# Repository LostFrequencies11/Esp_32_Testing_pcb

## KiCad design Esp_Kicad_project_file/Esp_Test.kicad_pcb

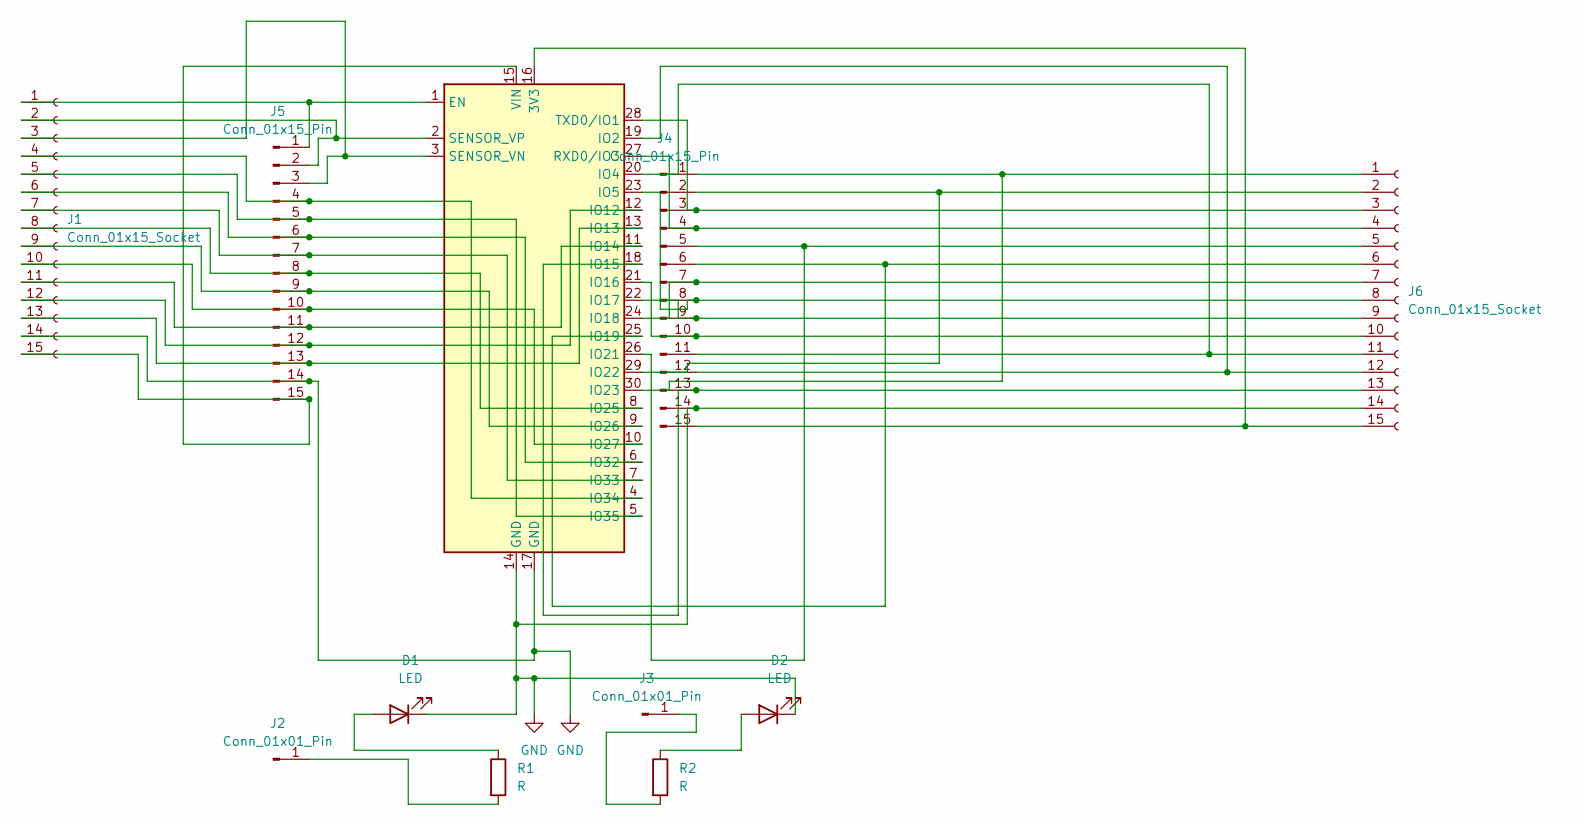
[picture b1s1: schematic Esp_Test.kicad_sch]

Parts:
D1, D2: LED; LED_D5.0mm_Clear
J1, J6: Conn_01x15_Socket; PinHeader_1x15_P2.54mm_Vertical
J2, J3: Conn_01x01_Pin; PinHeader_1x01_P2.54mm_Vertical
J4, J5: Conn_01x15_Pin; Molex_KK-254_AE-6410-15A_1x15_P2.54mm_Vertical
R1, R2: R; R_Axial_DIN0204_L3.6mm_D1.6mm_P7.62mm_Horizontal
U1: ESP32_DevKit_V1_DOIT; esp32_devkit_v1_doit

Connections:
GND: D1.1 (K), D2.1 (K), J1.14, J4.14, J5.14, J6.14, U1.14 (GND), U1.17 (GND)
unnamed: D1.2 (A), R1.1
unnamed: D2.2 (A), R2.1
unnamed: J1.1, J5.1, U1.1 (EN)
unnamed: J1.2, J5.2, U1.2 (SENSOR_VP)
unnamed: J1.3, J5.3, U1.3 (SENSOR_VN)
unnamed: J1.4, J5.4, U1.4 (IO34)
unnamed: J1.5, J5.5, U1.5 (IO35)
unnamed: J1.6, J5.6, U1.6 (IO32)
unnamed: J1.7, J5.7, U1.7 (IO33)
unnamed: J1.8, J5.8, U1.8 (IO25)
unnamed: J1.9, J5.9, U1.9 (IO26)
unnamed: J1.10, J5.10, U1.10 (IO27)
unnamed: J1.11, J5.11, U1.11 (IO14)
unnamed: J1.12, J5.12, U1.12 (IO12)
unnamed: J1.13, J5.13, U1.13 (IO13)
unnamed: J1.15, J5.15, U1.15 (VIN)
unnamed: J2.1, R1.2
unnamed: J3.1, R2.2
unnamed: J4.1, J6.1, U1.30 (IO23)
unnamed: J4.2, J6.2, U1.29 (IO22)
unnamed: J4.3, J6.3, U1.28 (TXD0/IO1)
unnamed: J4.4, J6.4, U1.27 (RXD0/IO3)
unnamed: J4.5, J6.5, U1.26 (IO21)
unnamed: J4.6, J6.6, U1.25 (IO19)
unnamed: J4.7, J6.7, U1.24 (IO18)
unnamed: J4.8, J6.8, U1.23 (IO5)
unnamed: J4.9, J6.9, U1.22 (IO17)
unnamed: J4.10, J6.10, U1.21 (IO16)
unnamed: J4.11, J6.11, U1.20 (IO4)
unnamed: J4.12, J6.12, U1.19 (IO2)
unnamed: J4.13, J6.13, U1.18 (IO15)
unnamed: J4.15, J6.15, U1.16 (3V3)

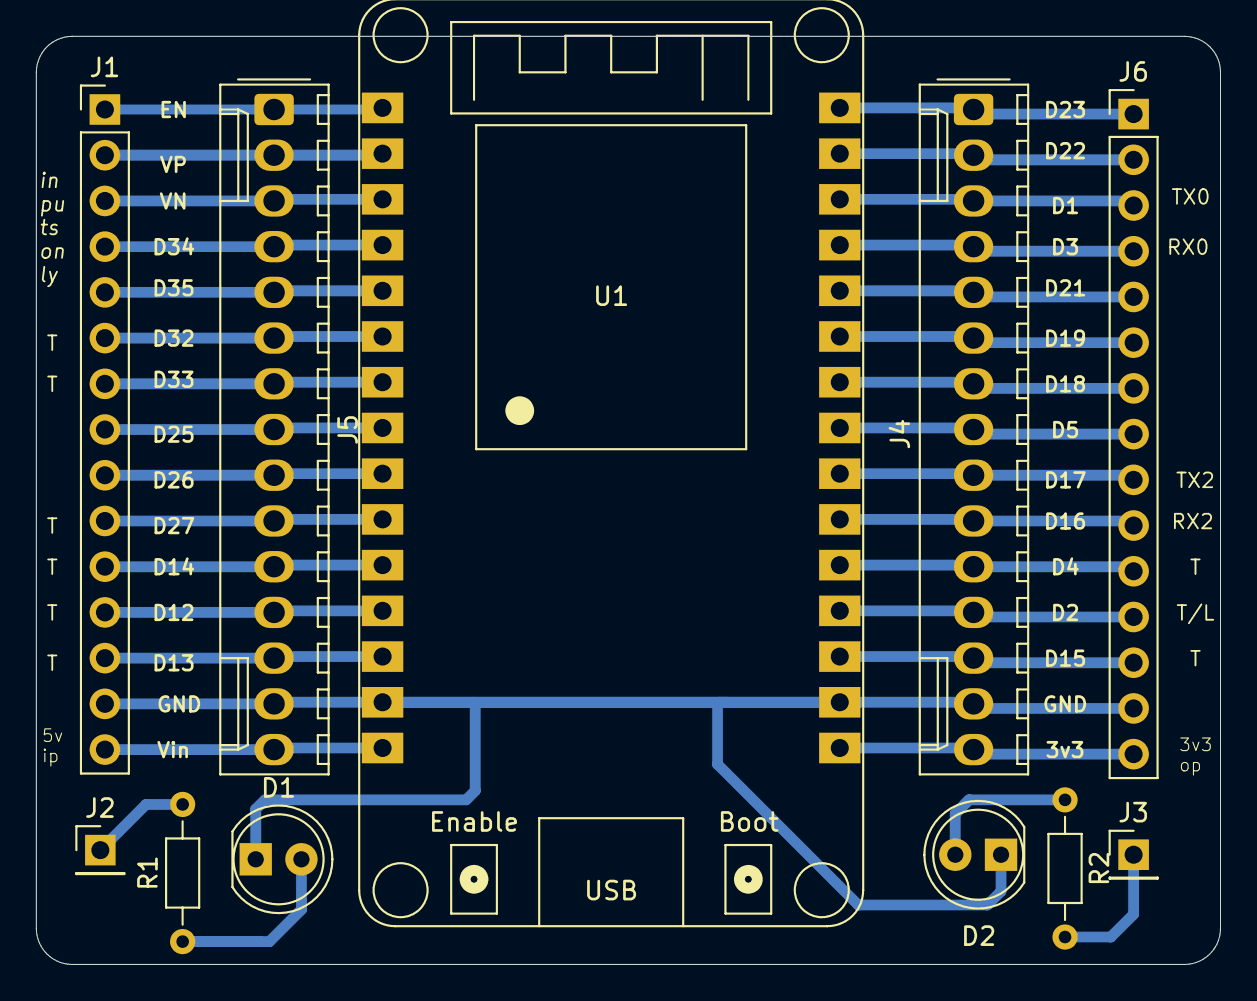
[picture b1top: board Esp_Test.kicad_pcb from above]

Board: 2 copper layers, 65.8 x 51.6 mm, 11 parts (0 on the bottom side), 33 nets.

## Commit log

2025-01-26 file data
